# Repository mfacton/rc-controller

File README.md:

# rc-controller

## General use STM32 based 2.4GHz rf transciever
Some inspiration from [DIY Arduino RC Transmitter](https://howtomechatronics.com/projects/diy-arduino-rc-transmitter/)

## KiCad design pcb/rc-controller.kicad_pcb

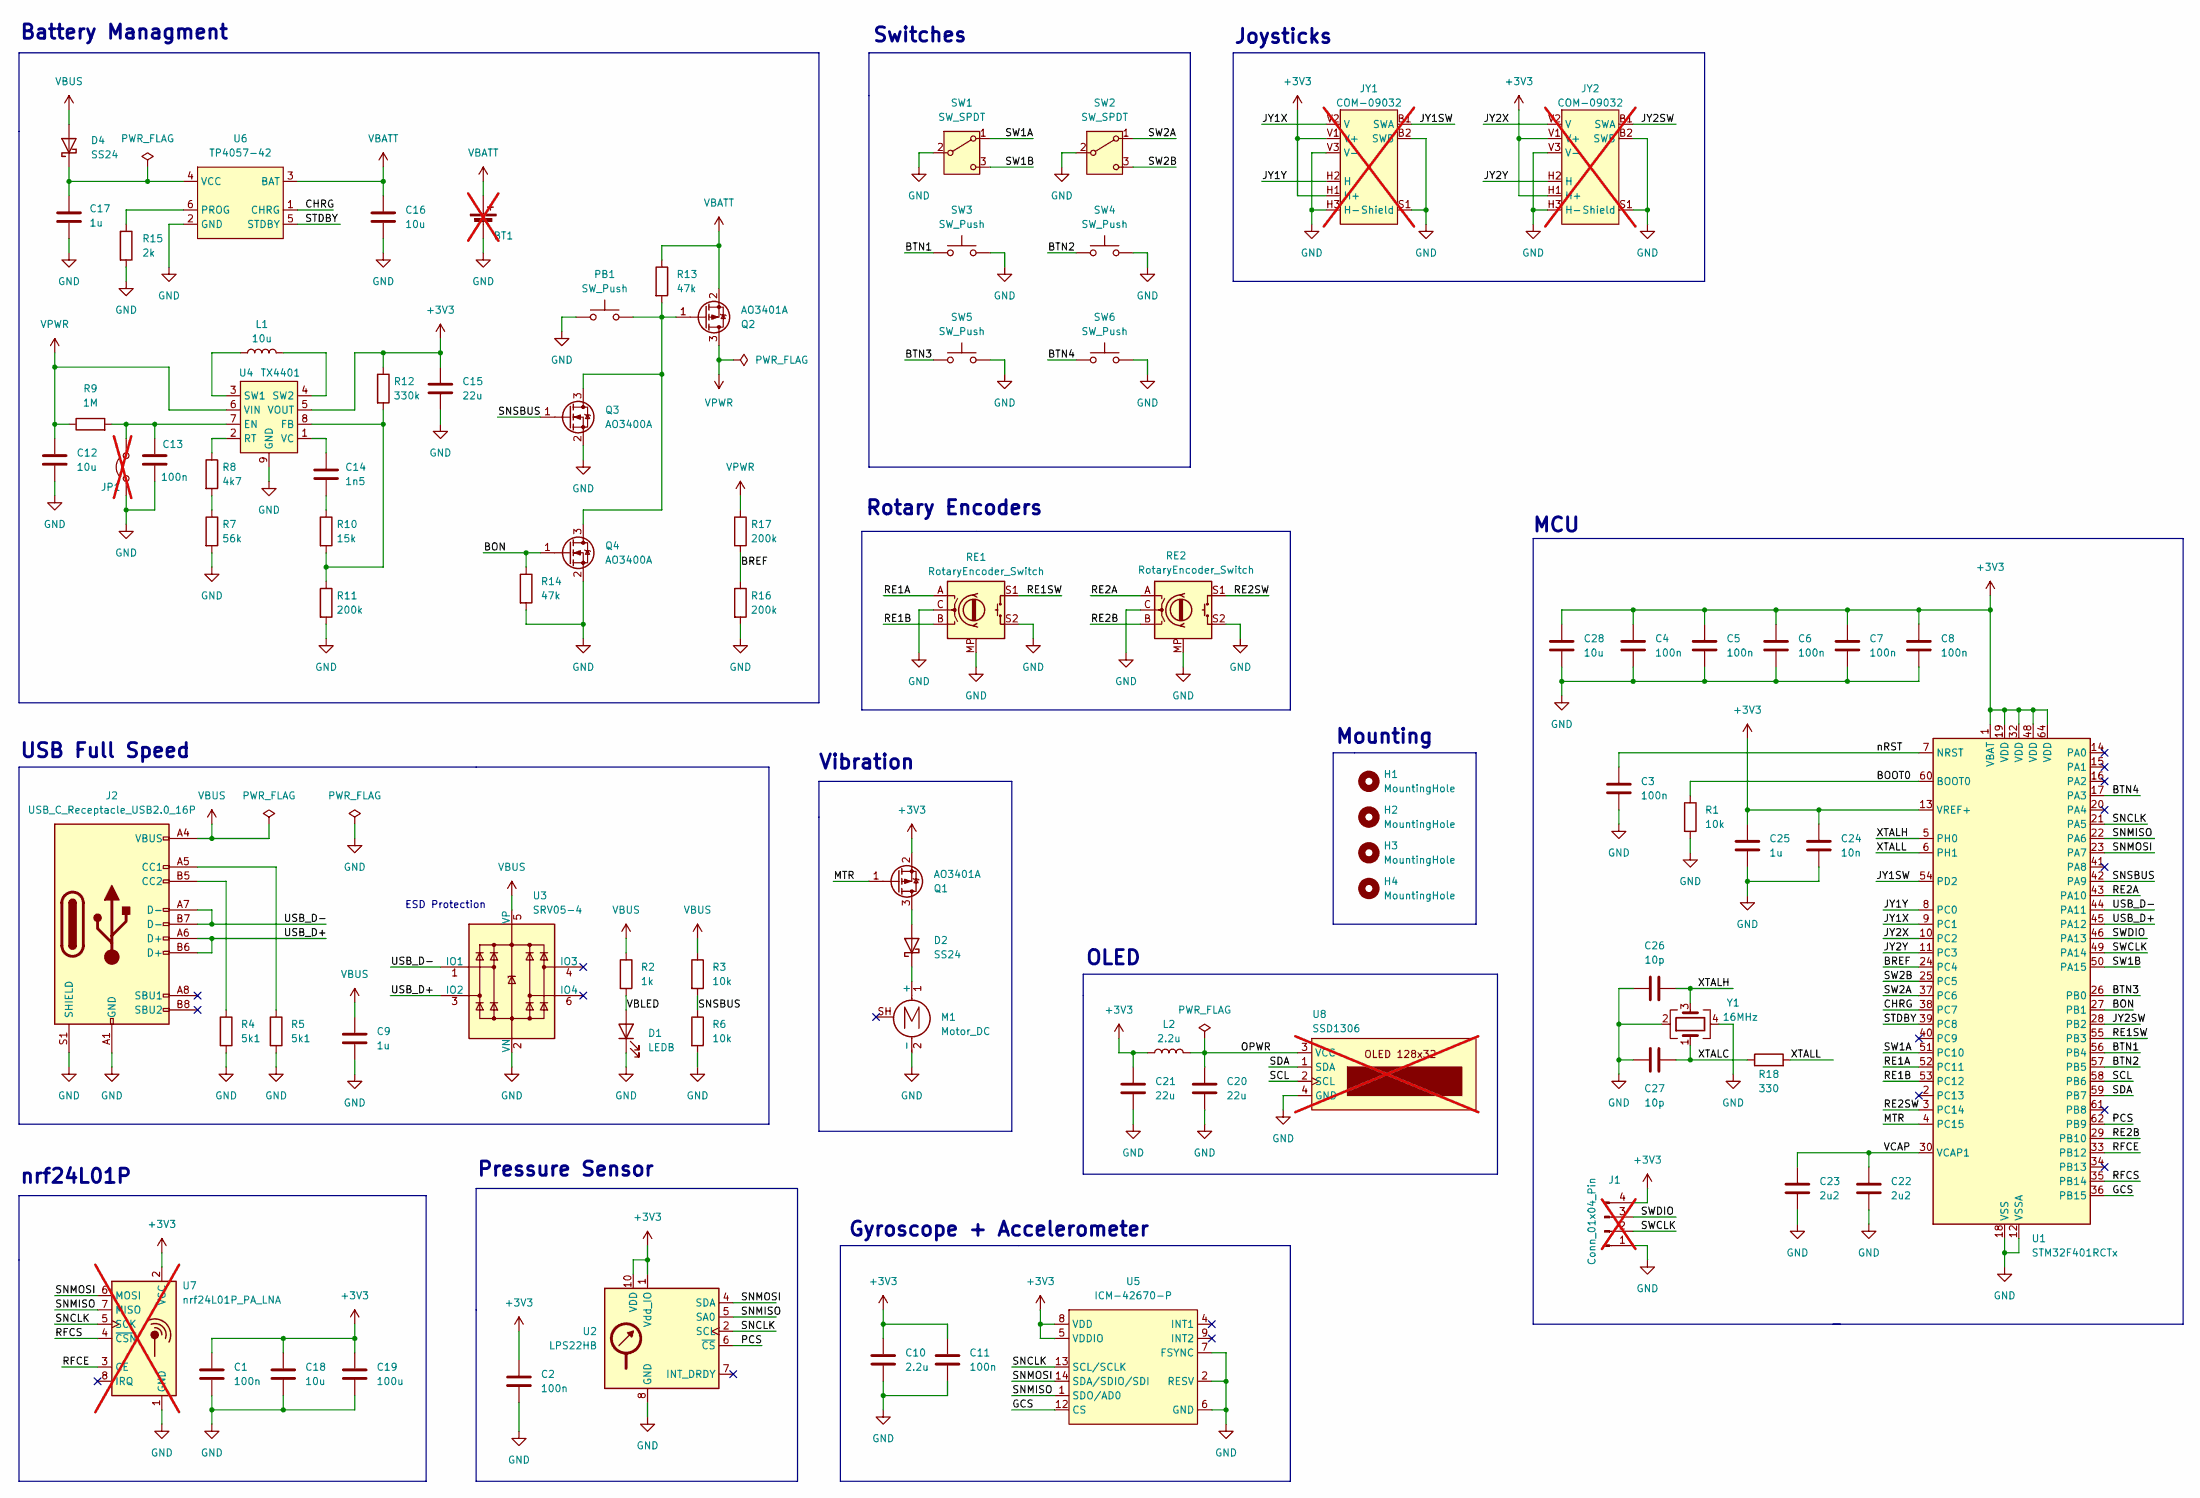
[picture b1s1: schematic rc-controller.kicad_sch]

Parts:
BT1: Battery_Cell; PinHeader_1x02_P2.54mm_Vertical; not fitted
C1, C2, C3, C4, C5, C6, C7, C8, C11, C13: 100n; C_0402_1005Metric
C9, C17, C25: 1u; C_0402_1005Metric
C10: 2.2u; C_0603_1608Metric
C12: 10u; C_0603_1608Metric; LCSC C19702
C14: 1n5; C_0603_1608Metric; LCSC C1595
C15, C20, C21: 22u; C_0603_1608Metric
C16, C18: 10u; C_0603_1608Metric
C19: 100u; C_1206_3216Metric
C22, C23: 2u2; C_0402_1005Metric
C24: 10n; C_0402_1005Metric
C26, C27: 10p; C_0402_1005Metric
C28: 10u; C_0402_1005Metric
D1: LEDB; LED_0603_1608Metric
D2, D4: SS24; D_SMA; LCSC C7420362
H1, H2, H3, H4: MountingHole; MountingHole_3.2mm_M3
J1: Conn_01x04_Pin; PinHeader_1x04_P2.54mm_Horizontal; not fitted
J2: USB_C_Receptacle_USB2.0_16P; USB_C_Receptacle_GCT_USB4105-xx-A_16P_TopMnt_Horizontal; LCSC C165948
JP1: Jumper_2_Open; SolderJumper-2_P1.3mm_Open_RoundedPad1.0x1.5mm; not fitted
JY1, JY2: COM-09032; not fitted
L1: 10u; L_1206_3216Metric; LCSC C395029
L2: 2.2u; L_0805_2012Metric; LCSC C1043
M1: Motor_DC; Vybronics_VZ30C1T8219732L; LCSC C2894731
PB1: SW_Push; SW_PUSH_6mm_H13mm; LCSC C2834892
Q1, Q2: AO3401A; SOT-23
Q3, Q4: AO3400A; SOT-23
R1, R3, R6: 10k; R_0402_1005Metric
R2: 1k; R_0402_1005Metric
R4, R5: 5k1; R_0402_1005Metric
R7: 56k; R_0402_1005Metric
R8: 4k7; R_0402_1005Metric
R9: 1M; R_0402_1005Metric; LCSC C26083
R10: 15k; R_0402_1005Metric
R11, R16, R17: 200k; R_0402_1005Metric
R12: 330k; R_0402_1005Metric; LCSC C25778
R13, R14: 47k; R_0402_1005Metric
R15: 2k; R_0402_1005Metric
R18: 330; R_0402_1005Metric
RE1, RE2: RotaryEncoder_Switch; RotaryEncoder_Alps_EC11E-Switch_Vertical_H20mm; LCSC C202365
SW1, SW2: SW_SPDT; 2MS; LCSC C908281
SW3, SW4, SW5, SW6: SW_Push; SW_PUSH_6mm_H13mm; LCSC C2834892
U1: STM32F401RCTx; LQFP-64_10x10mm_P0.5mm; LCSC C74524
U2: LPS22HB; ST_HLGA-10_2x2mm_P0.5mm_LayoutBorder3x2y; LCSC C94049
U3: SRV05-4; SOT-23-6; LCSC C7420376
U4: TX4401; HSOP-8-1EP_3.9x4.9mm_P1.27mm_EP2.41x3.1mm; LCSC C448642
U5: ICM-42670-P; LGA-14_3x2.5mm_P0.5mm_LayoutBorder3x4y
U6: TP4057-42; SOT-23-6
U7: nrf24L01P_PA_LNA; PinHeader_2x04_P2.54mm_Vertical; not fitted
U8: SSD1306; PinHeader_1x04_P2.54mm_Vertical; not fitted
Y1: 16MHz; Crystal_SMD_3225-4Pin_3.2x2.5mm

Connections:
+3V3: C1.1, C2.1, C4.1, C5.1, C6.1, C7.1, C8.1, C10.1, C11.1, C15.1, C18.1, C19.1, C21.1, C24.1, C25.1, C28.1, J1.4, JY1.H1 (H+), JY1.V1 (V+), JY2.H1 (H+), JY2.V1 (V+), L2.1, Q1.2 (S), R12.1, U1.1 (VBAT), U1.13 (VREF+), U1.19 (VDD), U1.32 (VDD), U1.48 (VDD), U1.64 (VDD), U2.1 (Vdd_IO), U2.10 (VDD), U4.5 (VOUT), U5.5 (VDDIO), U5.8 (VDD), U7.2 (VCC)
/BON: Q4.1 (G), R14.1, U1.27 (PB1)
/BOOT0: R1.1, U1.60 (BOOT0)
/BREF: R16.1, R17.2, U1.24 (PC4)
/BTN1: SW3.1, U1.56 (PB4)
/BTN2: SW4.1, U1.57 (PB5)
/BTN3: SW5.1, U1.26 (PB0)
/BTN4: SW6.1, U1.17 (PA3)
/CHRG: U1.38 (PC7), U6.1 (CHRG)
/GCS: U1.36 (PB15), U5.12 (CS)
/JY1SW: JY1.B1 (SWA), U1.54 (PD2)
/JY1X: JY1.V2 (V), U1.9 (PC1)
/JY1Y: JY1.H2 (H), U1.8 (PC0)
/JY2SW: JY2.B1 (SWA), U1.28 (PB2)
/JY2X: JY2.V2 (V), U1.10 (PC2)
/JY2Y: JY2.H2 (H), U1.11 (PC3)
/MTR: Q1.1 (G), U1.4 (PC15)
/OPWR: C20.1, L2.2, U8.3 (VCC)
/PCS: U1.62 (PB9), U2.6 (~CS)
/RE1A: RE1.A, U1.52 (PC11)
/RE1B: RE1.B, U1.53 (PC12)
/RE1SW: RE1.S1, U1.55 (PB3)
/RE2A: RE2.A, U1.43 (PA10)
/RE2B: RE2.B, U1.29 (PB10)
/RE2SW: RE2.S1, U1.3 (PC14)
/RFCE: U1.33 (PB12), U7.3 (CE)
/RFCS: U1.35 (PB14), U7.4 (~CSN)
/SCL: U1.58 (PB6), U8.2 (SCL)
/SDA: U1.59 (PB7), U8.1 (SDA)
/SNCLK: U1.21 (PA5), U2.2 (SCL), U5.13 (SCL/SCLK), U7.5 (SCK)
/SNMISO: U1.22 (PA6), U2.5 (SA0), U5.1 (SDO/AD0), U7.7 (MISO)
/SNMOSI: U1.23 (PA7), U2.4 (SDA), U5.14 (SDA/SDIO/SDI), U7.6 (MOSI)
/SNSBUS: Q3.1 (G), R3.2, R6.1, U1.42 (PA9)
/STDBY: U1.39 (PC8), U6.5 (STDBY)
/SW1A: SW1.1 (A), U1.51 (PC10)
/SW1B: SW1.3 (C), U1.50 (PA15)
/SW2A: SW2.1 (A), U1.37 (PC6)
/SW2B: SW2.3 (C), U1.25 (PC5)
/SWCLK: J1.2, U1.49 (PA14)
/SWDIO: J1.3, U1.46 (PA13)
/USB_D+: J2.A6 (D+), J2.B6 (D+), U1.45 (PA12), U3.3 (IO2)
/USB_D-: J2.A7 (D-), J2.B7 (D-), U1.44 (PA11), U3.1 (IO1)
/VBLED: D1.2 (A), R2.2
/VCAP: C22.1, C23.1, U1.30 (VCAP1)
/XTALC: C27.2, R18.1, Y1.1
/XTALH: C26.2, U1.5 (PH0), Y1.3
/XTALL: R18.2, U1.6 (PH1)
/nRST: C3.1, U1.7 (NRST)
GND: BT1.2 (-), C1.2, C2.2, C3.2, C4.2, C5.2, C6.2, C7.2, C8.2, C9.2, C10.2, C11.2, C12.2, C13.2, C15.2, C16.2, C17.2, C18.2, C19.2, C20.2, C21.2, C22.2, C23.2, C24.2, C25.2, C26.1, C27.1, C28.2, D1.1 (K), J1.1, J2.A1 (GND), J2.A12 (GND), J2.B1 (GND), J2.B12 (GND), J2.S1 (SHIELD), JP1.1 (A), JY1.B2 (SWB), JY1.H3 (H-), JY1.S1 (Shield), JY1.V3 (V-), JY2.B2 (SWB), JY2.H3 (H-), JY2.S1 (Shield), JY2.V3 (V-), M1.2 (-), PB1.1, Q3.2 (S), Q4.2 (S), R1.2, R4.2, R5.2, R6.2, R7.2, R11.2, R14.2, R15.2, R16.2, RE1.C, RE1.MP, RE1.S2, RE2.C, RE2.MP, RE2.S2, SW1.2 (B), SW2.2 (B), SW3.2, SW4.2, SW5.2, SW6.2, U1.12 (VSSA), U1.18 (VSS), U1.31 (VSS), U1.47 (VSS), U1.63 (VSS), U2.3 (GND), U2.8 (GND), U2.9 (GND), U3.2 (VN), U4.9 (GND), U5.2 (RESV), U5.3 (RESV), U5.6 (GND), U5.7 (FSYNC), U5.10 (RESV), U5.11 (RESV), U6.2 (GND), U7.1 (GND), U8.4 (GND), Y1.2, Y1.4
unnamed: C14.1, R10.1
unnamed: D2.2 (A), Q1.3 (D)
unnamed: D2.1 (K), M1.1 (+)
unnamed: C17.1, D4.1 (K), U6.4 (VCC)
unnamed: J2.A5 (CC1), R5.1
unnamed: J2.B5 (CC2), R4.1
unnamed: C13.1, JP1.2 (B), R9.2, U4.7 (EN)
unnamed: PB1.2, Q2.1 (G), Q3.3 (D), Q4.3 (D), R13.2
unnamed: R7.1, R8.2
unnamed: R10.2, R11.1, R12.2, U4.8 (FB)
unnamed: R8.1, U4.2 (RT)
unnamed: L1.1, U4.3 (SW1)
unnamed: L1.2, U4.4 (SW2)
unnamed: C14.2, U4.1 (VC)
unnamed: R15.1, U6.6 (PROG)
VBATT: BT1.1 (+), C16.1, Q2.2 (S), R13.1, U6.3 (BAT)
VBUS: C9.1, D4.2 (A), J2.A4 (VBUS), J2.A9 (VBUS), J2.B4 (VBUS), J2.B9 (VBUS), R2.1, R3.1, U3.5 (VP)
VPWR: C12.1, Q2.3 (D), R9.1, R17.1, U4.6 (VIN)

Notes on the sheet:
Mounting
Joysticks
Battery Managment
OLED
Vibration
Pressure Sensor
MCU
nrf24L01P
USB Full Speed
Rotary Encoders
Gyroscope + Accelerometer
Switches
ESD Protection

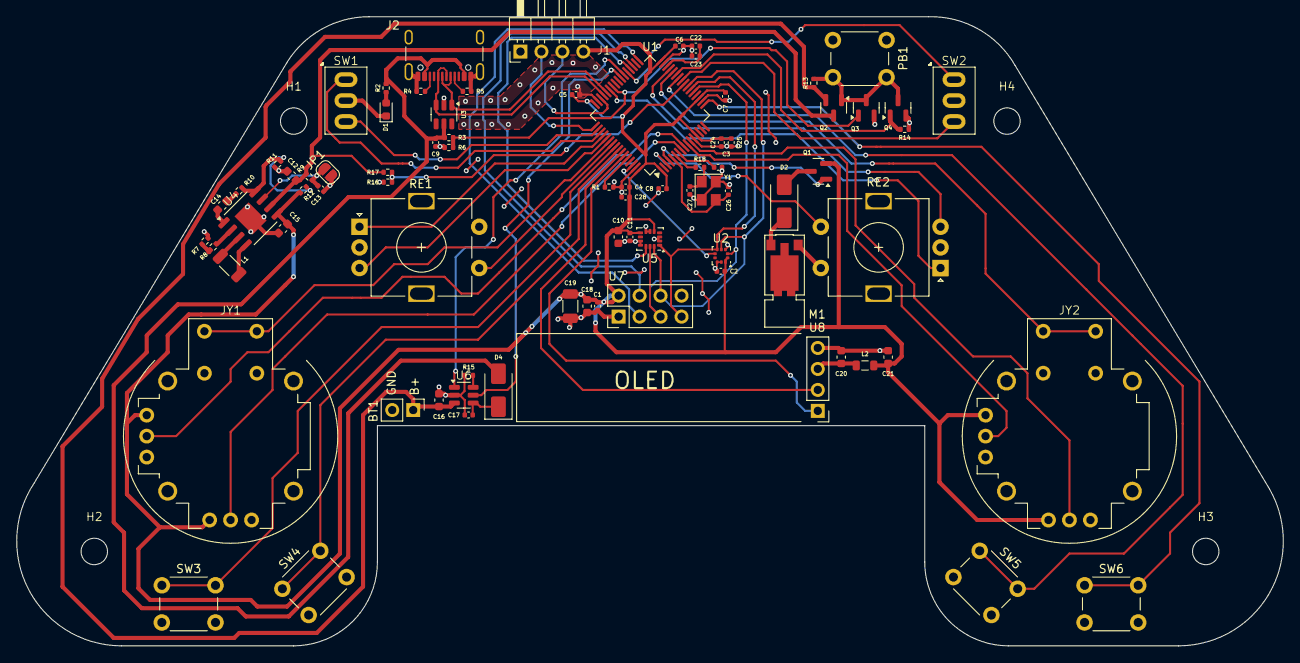
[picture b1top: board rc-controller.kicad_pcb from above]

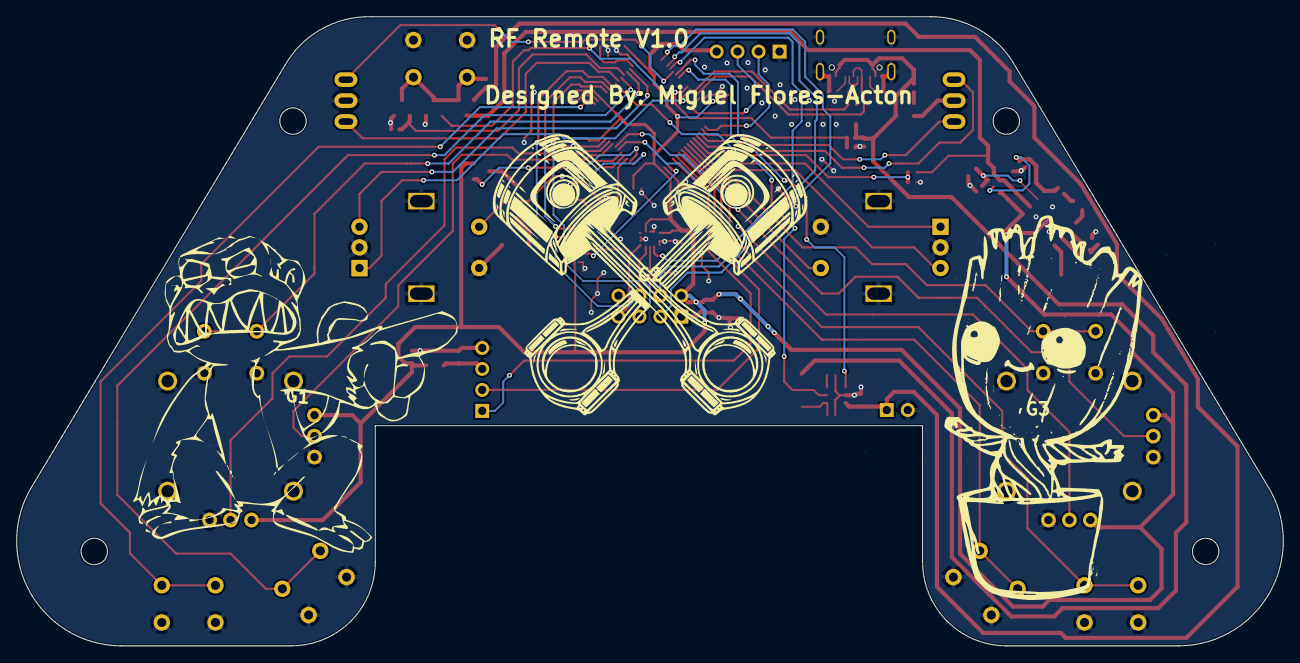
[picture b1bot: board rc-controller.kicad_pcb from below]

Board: 2 copper layers, 153.4 x 76.2 mm, 87 parts (3 on the bottom side), 67 nets.

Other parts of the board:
G1: Monkey; LOGO
G2: Engine; LOGO
G3: GROOT; LOGO

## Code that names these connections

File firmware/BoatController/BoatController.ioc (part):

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Mcu.Name=STM32F401R(B-C)Tx
Mcu.Package=LQFP64
Mcu.UserName=STM32F401RCTx
PA10.GPIOParameters=GPIO_PuPd,GPIO_Label
PA10.GPIO_Label=RE2A
PA10.GPIO_PuPd=GPIO_PULLUP
PA10.Signal=GPIO_Input
PA11.Mode=Device_Only
PA11.Signal=USB_OTG_FS_DM
PA12.Mode=Device_Only
PA12.Signal=USB_OTG_FS_DP
PA13.Mode=Serial_Wire
PA13.Signal=SYS_JTMS-SWDIO
PA14.Mode=Serial_Wire
PA14.Signal=SYS_JTCK-SWCLK
PA15.GPIOParameters=GPIO_PuPd,GPIO_Label
PA15.GPIO_Label=SW1B
PA15.GPIO_PuPd=GPIO_PULLUP
PA15.Signal=GPIO_Input
PA3.GPIOParameters=GPIO_PuPd,GPIO_Label
PA3.GPIO_Label=BTN4
PA3.GPIO_PuPd=GPIO_PULLUP
PA3.Signal=GPIO_Input
PA5.Mode=Full_Duplex_Master
PA5.Signal=SPI1_SCK
PA6.Mode=Full_Duplex_Master
PA6.Signal=SPI1_MISO
PA7.Mode=Full_Duplex_Master
PA7.Signal=SPI1_MOSI
PA9.Mode=Activate_VBUS
PA9.Signal=USB_OTG_FS_VBUS
PB0.GPIOParameters=GPIO_PuPd,GPIO_Label
PB0.GPIO_Label=BTN3
PB0.GPIO_PuPd=GPIO_PULLUP
PB0.Signal=GPIO_Input
PB1.GPIOParameters=GPIO_Speed,PinState,GPIO_Label
PB1.GPIO_Label=BTNON
PB1.GPIO_Speed=GPIO_SPEED_FREQ_MEDIUM
PB1.PinState=GPIO_PIN_SET
PB1.Signal=GPIO_Output
PB10.GPIOParameters=GPIO_PuPd,GPIO_Label
PB10.GPIO_Label=RE2B
PB10.GPIO_PuPd=GPIO_PULLUP
PB10.Signal=GPIO_Input
PB12.GPIOParameters=GPIO_Speed,GPIO_Label
PB12.GPIO_Label=RFCE
PB12.GPIO_Speed=GPIO_SPEED_FREQ_VERY_HIGH
PB12.Signal=GPIO_Output
PB14.GPIOParameters=GPIO_Speed,PinState,GPIO_Label
PB14.GPIO_Label=RFCS
PB14.GPIO_Speed=GPIO_SPEED_FREQ_VERY_HIGH
PB14.PinState=GPIO_PIN_SET
PB14.Signal=GPIO_Output
PB15.GPIOParameters=GPIO_Speed,PinState,GPIO_Label
PB15.GPIO_Label=GCS
PB15.GPIO_Speed=GPIO_SPEED_FREQ_VERY_HIGH
PB15.PinState=GPIO_PIN_SET
PB15.Signal=GPIO_Output
PB2.GPIOParameters=GPIO_PuPd,GPIO_Label
PB2.GPIO_Label=JY2SW
PB2.GPIO_PuPd=GPIO_PULLUP
PB2.Signal=GPIO_Input
PB3.GPIOParameters=GPIO_PuPd,GPIO_Label
PB3.GPIO_Label=RE1SW
PB3.GPIO_PuPd=GPIO_PULLUP
PB3.Signal=GPIO_Input
PB4.GPIOParameters=GPIO_PuPd,GPIO_Label
PB4.GPIO_Label=BTN1
PB4.GPIO_PuPd=GPIO_PULLUP
PB4.Signal=GPIO_Input
PB5.GPIOParameters=GPIO_PuPd,GPIO_Label
PB5.GPIO_Label=BTN2
PB5.GPIO_PuPd=GPIO_PULLUP
PB5.Signal=GPIO_Input
PB6.Mode=I2C
PB6.Signal=I2C1_SCL
PB7.Mode=I2C
PB7.Signal=I2C1_SDA
PB9.GPIOParameters=GPIO_Speed,PinState,GPIO_Label
PB9.GPIO_Label=PCS
PB9.GPIO_Speed=GPIO_SPEED_FREQ_VERY_HIGH
PB9.PinState=GPIO_PIN_SET
PB9.Signal=GPIO_Output
PC0.GPIOParameters=GPIO_Label
PC0.GPIO_Label=JY1Y
PC0.Signal=ADCx_IN10
PC1.GPIOParameters=GPIO_Label
PC1.GPIO_Label=JY1X
PC1.Signal=ADCx_IN11
PC10.GPIOParameters=GPIO_PuPd,GPIO_Label
PC10.GPIO_Label=SW1A
PC10.GPIO_PuPd=GPIO_PULLUP
PC10.Signal=GPIO_Input
PC11.GPIOParameters=GPIO_PuPd,GPIO_Label
PC11.GPIO_Label=RE1A
PC11.GPIO_PuPd=GPIO_PULLUP
PC11.Signal=GPIO_Input
PC12.GPIOParameters=GPIO_PuPd,GPIO_Label
PC12.GPIO_Label=RE1B
PC12.GPIO_PuPd=GPIO_PULLUP
PC12.Signal=GPIO_Input
PC14-OSC32_IN.GPIOParameters=GPIO_PuPd,GPIO_Label
PC14-OSC32_IN.GPIO_Label=RE2SW
PC14-OSC32_IN.GPIO_PuPd=GPIO_PULLUP
PC14-OSC32_IN.Signal=GPIO_Input
PC15-OSC32_OUT.GPIOParameters=GPIO_Speed,PinState,GPIO_PuPd,GPIO_Label
PC15-OSC32_OUT.GPIO_Label=MTR
PC15-OSC32_OUT.GPIO_PuPd=GPIO_NOPULL
PC15-OSC32_OUT.GPIO_Speed=GPIO_SPEED_FREQ_LOW
PC15-OSC32_OUT.PinState=GPIO_PIN_SET
PC15-OSC32_OUT.Signal=GPIO_Output
PC2.GPIOParameters=GPIO_Label
PC2.GPIO_Label=JY2X
PC2.Signal=ADCx_IN12
PC3.GPIOParameters=GPIO_Label
PC3.GPIO_Label=JY2Y
PC3.Signal=ADCx_IN13
PC4.GPIOParameters=GPIO_Label
PC4.GPIO_Label=BREF
PC4.Signal=ADCx_IN14
PC5.GPIOParameters=GPIO_PuPd,GPIO_Label
PC5.GPIO_Label=SW2B
PC5.GPIO_PuPd=GPIO_PULLUP
PC5.Signal=GPIO_Input
PC6.GPIOParameters=GPIO_PuPd,GPIO_Label
PC6.GPIO_Label=SW2A
PC6.GPIO_PuPd=GPIO_PULLUP
PC6.Signal=GPIO_Input
PC7.GPIOParameters=GPIO_PuPd,GPIO_Label
PC7.GPIO_Label=CHRG
PC7.GPIO_PuPd=GPIO_PULLUP
PC7.Signal=GPIO_Input
PC8.GPIOParameters=GPIO_PuPd,GPIO_Label
PC8.GPIO_Label=STBY
PC8.GPIO_PuPd=GPIO_PULLUP
PC8.Signal=GPIO_Input
PD2.GPIOParameters=GPIO_PuPd,GPIO_Label
PD2.GPIO_Label=JY1SW
PD2.GPIO_PuPd=GPIO_PULLUP
PD2.Signal=GPIO_Input
PH0\ -\ OSC_IN.Mode=HSE-External-Oscillator
PH0\ -\ OSC_IN.Signal=RCC_OSC_IN
PH1\ -\ OSC_OUT.Mode=HSE-External-Oscillator
PH1\ -\ OSC_OUT.Signal=RCC_OSC_OUT
RCC.HSE_VALUE=16000000
RCC.SYSCLKFreq_VALUE=84000000
RCC.SYSCLKSource=RCC_SYSCLKSOURCE_PLLCLK
board=custom

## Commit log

2024-04-18 init kicad project
2024-04-18 Restructure project
2024-04-18 Add pcb bom materials
2024-04-19 Remove autosave files
2024-04-19 Change OLED
2024-04-19 Fix OLED link
2024-04-19 Change joystick
2024-04-19 Add joystick caps
2024-04-19 Finish schematic
2024-04-19 Create STM32 project
2024-04-19 Add gitignore
2024-04-19 Remove STMCube metadata
2024-04-19 Move all gitignores to global
2024-04-19 Fix gitignore for kicad autosave file
2024-04-19 Remove kicad autosave file
2024-04-20 Add crystal oscillator
2024-04-20 Configure USB
2024-04-20 Organize pin functions
2024-04-20 Assign basic footprints
2024-04-23 Finish mapping footprints
2024-04-24 Finish rough layout
2024-04-25 Final placement before routing
2024-04-26 Add net classes
2024-04-26 Add net classes for pcb
2024-04-26 Finish layout
2024-04-26 Add silkscreen
2024-04-26 Fix bom and generate fab files
2024-05-02 Initialize stm32 project and fix vref issue
2024-05-09 Remove kicad refrences
2024-05-09 Revert global gitignore
2024-05-09 Remake STM32 project
2024-05-09 Finish STM32Cube setup
2024-05-09 Add step file
2024-05-12 Add modules and basic rc control
2024-05-12 Kicad autosave
2024-05-14 Remove and ignore autogenerated stm32 code
2024-05-20 Update charging circuitry
2024-06-06 Remove OS garbage
2024-06-06 Save
2024-06-06 Re-add ignored file
